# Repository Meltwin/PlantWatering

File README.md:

<h1 align="center">
    Automatic plant watering system
</h1>

This project consist of making an automated watering system for my plants. It works with an ESP-32 board that controls a 5V pump. This repository contains:

- The electrical schematic (made in KiCAD) that can be found in the `KiCAD` folder,
- The code for the ESP-32 board in the `plant_watering` folder,

The project was tested and made on a ESP-WROOM-32 board.

Distributed under the MIT licence. Copyright (c) 2024 Meltwin

## Hardware description

The parts used here are:

- an ESP32 board,
- a dual MOFSET driver,
- USB-C female port for power input,
- Barrel Jack female port for power output (for the pump)

## Software description

The software available here control a 5V pump through the dual MOSFET driver with a PWM signal. There two main parameter for controlling the pump behaviour: the **opened time** and the **opened frequency**. This way people can freely choose the quantity of water to actually drop according to the type of plant.

This data will be stored onto the ESP controller internal storage so that it survive power disconnect.

## Online resources used

- [ESP-32 Getting Started - Expressif](https://docs.espressif.com/projects/esp-idf/en/stable/esp32/hw-reference/esp32/get-started-devkitc.html)
- [ESP-32 Pinout - Last Minute Engineers](https://lastminuteengineers.com/esp32-pinout-reference/)
- [PWN usage - Upesy (FR only)](https://www.upesy.fr/blogs/tutorials/how-to-use-pwm-on-esp32-with-examples)
- [ADC usage - Last Minute Engineers](https://lastminuteengineers.com/esp32-basics-adc/)

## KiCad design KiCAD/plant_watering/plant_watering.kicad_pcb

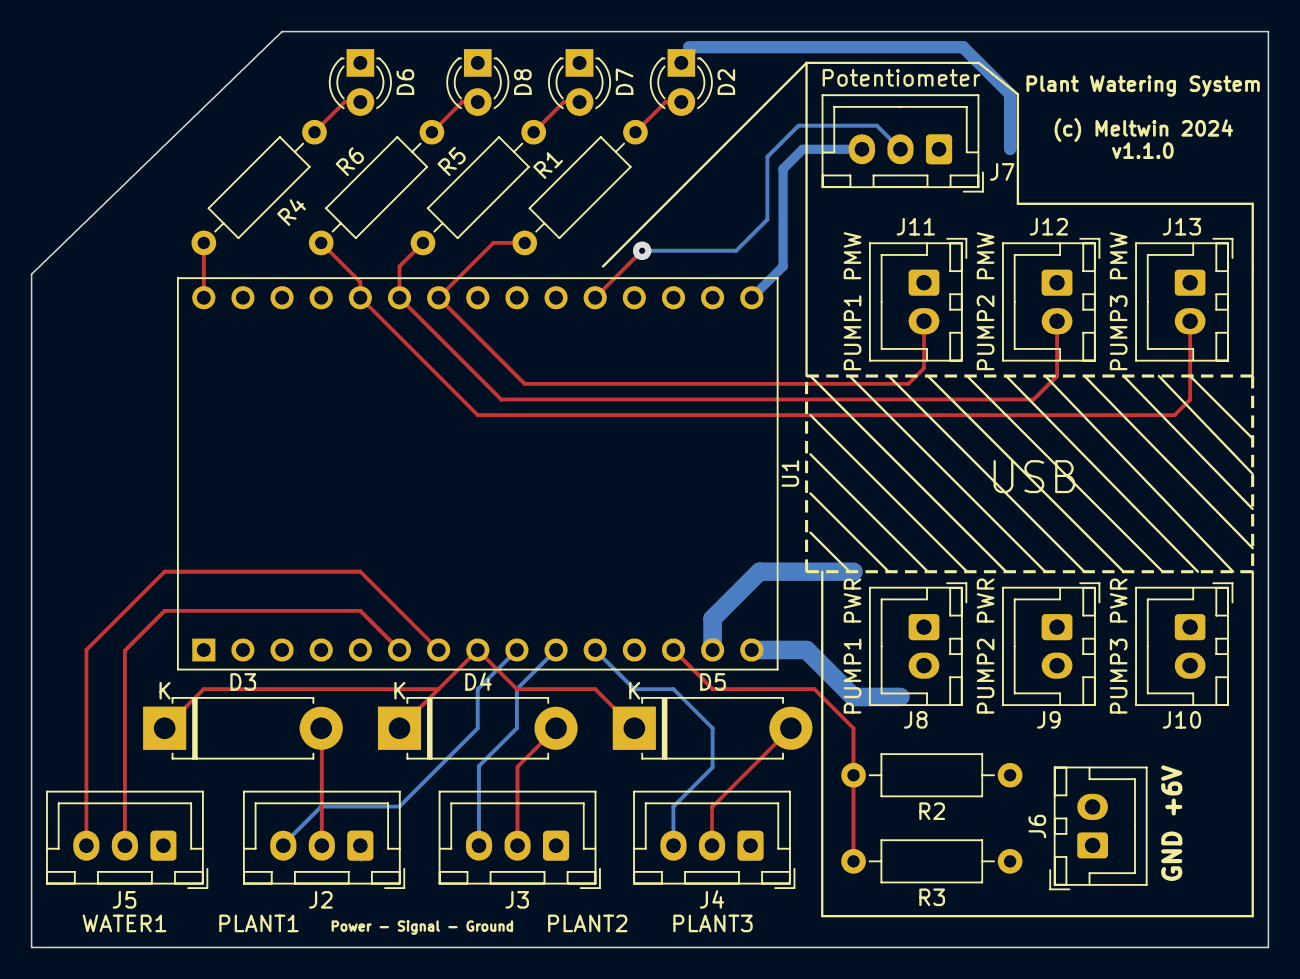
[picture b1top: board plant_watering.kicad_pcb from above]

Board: 2 copper layers, 80.3 x 59.4 mm, 26 parts (0 on the bottom side), 22 nets.

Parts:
D2, D6, D7, D8: LED; LED_D3.0mm
D3, D4, D5: D; D_5W_P10.16mm_Horizontal
J2: PLANT1; JST_XH_B3B-XH-A_1x03_P2.50mm_Vertical
J3: PLANT2; JST_XH_B3B-XH-A_1x03_P2.50mm_Vertical
J4: PLANT3; JST_XH_B3B-XH-A_1x03_P2.50mm_Vertical
J5: WATER1; JST_XH_B3B-XH-A_1x03_P2.50mm_Vertical
J6: 4xLR6 1.5V Battery Pack; JST_XH_B2B-XH-A_1x02_P2.50mm_Vertical
J7: Potentiometer; JST_XH_B3B-XH-A_1x03_P2.50mm_Vertical
J8: PUMP1 PWR; JST_XH_B2B-XH-A_1x02_P2.50mm_Vertical
J9: PUMP2 PWR; JST_XH_B2B-XH-A_1x02_P2.50mm_Vertical
J10: PUMP3 PWR; JST_XH_B2B-XH-A_1x02_P2.50mm_Vertical
J11: PUMP1 PMW; JST_XH_B2B-XH-A_1x02_P2.50mm_Vertical
J12: PUMP2 PMW; JST_XH_B2B-XH-A_1x02_P2.50mm_Vertical
J13: PUMP3 PMW; JST_XH_B2B-XH-A_1x02_P2.50mm_Vertical
R1, R4, R5, R6: 220Ω; R_Axial_DIN0207_L6.3mm_D2.5mm_P10.16mm_Horizontal
R2: R_Battery; R_Axial_DIN0207_L6.3mm_D2.5mm_P10.16mm_Horizontal
R3: R_battery; R_Axial_DIN0207_L6.3mm_D2.5mm_P10.16mm_Horizontal
U1: ESP32-WROOM-32; ESP32-C3-DevKitM-1

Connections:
+3V3: J7.3, U1.3V3 (VDD_3V)
+6V: J6.2, J8.2, J9.2, J10.2, R2.1, U1.VIN (VDD_5V)
/BAT_LVL_3V: R2.2, R3.2, U1.D13 (IO13/ADC2_4/HSPI_MOSI/Touch4)
/MANUAL_PWM: J7.2, U1.D4 (IO4/ADC2_0/Touch0)
/PLANT1_ENB: J2.3, U1.D26 (IO26/ADC2_9/DAC2)
/PLANT1_SIG: D3.2 (A), J2.2
/PLANT2_ENB: J3.3, U1.D27 (IO27/ADC2_7/Touch7)
/PLANT2_SIG: D4.2 (A), J3.2
/PLANT3_ENB: J4.3, U1.D14 (IO14/ADC2_6/HSPI_CLK/Touch6)
/PLANT3_SIG: D5.2 (A), J4.2
/PUMP1_PWM: J11.2, R1.1, U1.D18 (IO18/SPI_SCK/VSPI_SLK)
/PUMP2_PWM: J12.2, R5.1, U1.D19 (IO19/MISO/VSPI_MISO)
/PUMP3_PWM: J13.2, R6.1, U1.D21 (IO21/SDA)
/STATUS: R4.1, U1.D23 (IO23/SPI_MOSI/VSPI_MOSI)
/WATER_LEVEL_ENB: J5.3, U1.D33 (IO33/ADC1_5/Touch8)
/WATER_LEVEL_SIG: J5.2, U1.D32 (IO32/ADC1_4/Touch9)
GND: D2.1 (K), D6.1 (K), D7.1 (K), D8.1 (K), J2.1, J3.1, J4.1, J5.1, J6.1, J7.1, J8.1, J9.1, J10.1, J11.1, J12.1, J13.1, R3.1, U1.GND
unnamed: D2.2 (A), R1.2
unnamed: D3.1 (K), D4.1 (K), D5.1 (K), U1.D25 (IO25/ADC2_8/DAC1)
unnamed: D6.2 (A), R4.2
unnamed: D7.2 (A), R5.2
unnamed: D8.2 (A), R6.2

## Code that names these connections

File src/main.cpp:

/**
 *  ===========================================================================
 *                      Automated Plant Watering System
 *                     By Meltwin - 2024 (c) MIT Licence
 *  ============================================================================
 */

#include <Arduino.h>
#include "ApiCaller.hpp"
#include "IO/Pump.hpp"
#include "IO/Sensor.hpp"
#include "WifiConnect.hpp"
#include "common.hpp"

#include "datetime.h"
#include "dev_console.h"

// ----------------------------------------------------------------------------
// Parameters
// ----------------------------------------------------------------------------
#define WIFI_SSID "B-DTU Wireless"
#define WIFI_PSW "StudentDK"

// Sensors
#define BATTERY_SENSOR_DATA GPIO_NUM_13
#define PLANT1_SENSOR_ENABLE GPIO_NUM_26
#define PLANT2_SENSOR_ENABLE GPIO_NUM_27
#define PLANT3_SENSOR_ENABLE GPIO_NUM_14
#define PLANTS_SENSOR_DATA GPIO_NUM_25
#define WATER_LEVEL_ENABLE GPIO_NUM_33
#define WATER_LEVEL_DATA GPIO_NUM_32

// Pump
#define PUMP1_PWM_PIN GPIO_NUM_18
#define PUMP2_PWM_PIN GPIO_NUM_19
#define PUMP3_PWM_PIN GPIO_NUM_21
#define PUMP_PWM_CHANNEL 0
#define PUMP_PWM_FREQ 16000
#define PUMP_PWM_RESOLUTION 12

// ----------------------------------------------------------------------------
// Aliases
// ----------------------------------------------------------------------------
using meltwin::APICaller;
using meltwin::InternalErrors;
using meltwin::Pump;
using meltwin::PumpCmd;
using meltwin::Sensor;


bool console = false;

// ----------------------------------------------------------------------------
// Debug Console & Automatic Watering programs
// ----------------------------------------------------------------------------
void run_console() {
  do
    Serial.println("Waiting for next cmd ...");
  while (!meltwin::DevConsole::execute_command());
}

void run_watering() {
  // ============================================
  // I - Reading sensors
  // ============================================
  std::vector<Sensor> sensors{
    Sensor(BATTERY_SENSOR_DATA, 0.0, 6.0),
    Sensor(PLANTS_SENSOR_DATA, 0.0, 1.0, PLANT1_SENSOR_ENABLE),
    Sensor(PLANTS_SENSOR_DATA, 0.0, 1.0, PLANT2_SENSOR_ENABLE),
    Sensor(PLANTS_SENSOR_DATA, 0.0, 1.0, PLANT3_SENSOR_ENABLE),
    Sensor(WATER_LEVEL_DATA, 0.0, 1.0, WATER_LEVEL_ENABLE),
  };
  float values[sensors.size()];
  Serial.println("Reading sensors values");
  for (size_t i = 0; i < sensors.size(); i++) {
    Serial.printf("\t-> Reading sensor %zu ... ", i);
    auto& s = sensors[i];
    s.setup_sensor();
    values[i] = s.read_sensor();
    Serial.printf("%f\n", values[i]);
    s.cleanup();
  }

  // ============================================
  // II - Connect to API
  // ============================================
  Serial.println("Initializing WiFi");
  if (!init_wifi(WIFI_SSID, WIFI_PSW))
    return;

  Serial.println("Authenticating on the API");
  std::string token;
  if (auto code = APICaller::authenticate(token); code != InternalErrors::SUCCESS) {
    Serial.printf("\t-> Couldn't authenticate on API: error %d\n", code);
    return;
  }
  Serial.printf("\t-> The connction token is {%s}\n", token.c_str());

  // Upload sensors values
  Serial.println("Sending sensors data to the API");
  for (size_t i = 0; i < sensors.size(); i++) {
    Serial.printf("\t-> Sending data for sensor %zu\n", i);
    if (auto code = APICaller::sendData(token.c_str(), i, values[i]); code != InternalErrors::SUCCESS)
      Serial.printf("\t  Couldn't send sensor data on API: error %d\n", code);
  }

  // ============================================
  // III - Watering plants
  // ============================================
  std::vector<Pump> pumps{Pump(PUMP1_PWM_PIN, PUMP_PWM_CHANNEL, PUMP_PWM_RESOLUTION)};
  for (size_t i = 0; i < pumps.size(); i++) {
    auto& pump = pumps[i];
    PumpCmd cmd;
    APICaller::getPumpCmd(token.c_str(), i, cmd);

    // Power pump if needed
    if (cmd.time > 0.0 && cmd.pwm > 0.0) {
      Serial.printf("Running pump %zu for %f s at %f % ...\n", i, cmd.time, cmd.pwm);
      pump.setup_pump(PUMP_PWM_FREQ);
      pump.run_pump(cmd);
      pump.stop_pump();
    }
    APICaller::pumpingDone(token.c_str(), i);
  }
}

void wrap_up() {
  Serial.println("Wrapping up ...");

  delay(1000);
  digitalWrite(13, LOW);
  Serial.end();
  delay(1000);
  esp_sleep_enable_timer_wakeup(DEEP_SLEEP_DURATION);
  esp_deep_sleep_start();
}

// ----------------------------------------------------------------------------
// Setup
// ----------------------------------------------------------------------------
void setup() {

  // Setup sub classes
  Serial.begin(SERIAL_BAUD_RATE);

  // Setup deep sleep
  esp_sleep_enable_timer_wakeup(DEEP_SLEEP_DURATION);

  // Load activity pin
  pinMode(13, OUTPUT);
  digitalWrite(13, HIGH);

  // // Look for serial connection for preferences dev console
  Serial.printf("Send \"cmd\" to start developer console (%f s)\n", meltwin::DevConsole::START_TIMEOUT / 1000.);
  console = meltwin::DevConsole::wait_for_console_launch();

  (console) ? run_console() : run_watering();
  wrap_up();
}

void loop() {}

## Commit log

2024-05-18 Beginning of electrical schematic
2024-05-18 Added a readme
2024-05-18 Base ESP32 script
2024-05-22 PWM working + Manual input working as well
2024-12-18 API Exchange
